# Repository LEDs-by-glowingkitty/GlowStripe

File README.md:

# GlowStripe PCB

## What is this project?

A stable LED stripe PCB with a separate trace for a button.

## Links

- [Schematic](https://github.com/glowingkitty/GlowStripe/blob/main/GlowLEDsPCB.pdf)
- [Interactive BOM](https://htmlpreview.github.io/?https://github.com/glowingkitty/GlowStripe/blob/main/bom/ibom.html)
- [PCB stencils](https://github.com/glowingkitty/GlowStripe/tree/main/PCB%20stencils)

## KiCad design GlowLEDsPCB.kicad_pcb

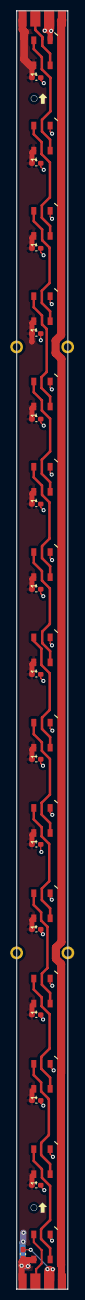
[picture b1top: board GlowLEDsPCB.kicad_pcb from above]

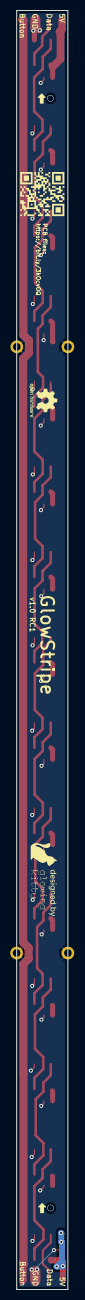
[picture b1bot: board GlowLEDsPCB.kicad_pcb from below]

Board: 2 copper layers, 10.0 x 250.0 mm, 43 parts (5 on the bottom side), 19 nets.

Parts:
C1, C2, C3, C4, C5, C6, C7, C8, C9, C10, C11, C12, C13, C14, C15: 0.1uf; C_0603_1608Metric_Pad1.08x0.95mm_HandSolder
D1, D2, D3, D4, D5, D6, D7, D8, D9, D10, D11, D12, D13, D14, D15: WS2812B; LED_WS2812B_PLCC4_5.0x5.0mm_P3.2mm
H1, H2, H3, H4: Castellated_hole; Castellated hole
OSHW logo: OSHW-Logo2_7.3x6mm_SilkScreen
U1, U2: Contact pads; LED strip connector 4pad small
designedby: LOGO
leddirectionarrow4, leddirectionarrow4#2, leddirectionarrow4#3, leddirectionarrow4#4: LOGO
qrcode: LOGO

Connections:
+5V: C1.1, C2.1, C3.1, C4.1, C5.1, C6.1, C7.1, C8.1, C9.1, C10.1, C11.1, C12.1, C13.1, C14.1, C15.1, D1.1 (VDD), D2.1 (VDD), D3.1 (VDD), D4.1 (VDD), D5.1 (VDD), D6.1 (VDD), D7.1 (VDD), D8.1 (VDD), D9.1 (VDD), D10.1 (VDD), D11.1 (VDD), D12.1 (VDD), D13.1 (VDD), D14.1 (VDD), D15.1 (VDD), U1.1 (5V), U2.1 (5V)
BUTTON: U1.4 (BUTTON), U2.4 (BUTTON)
GND: C1.2, C2.2, C3.2, C4.2, C5.2, C6.2, C7.2, C8.2, C9.2, C10.2, C11.2, C12.2, C13.2, C14.2, C15.2, D1.3 (VSS), D2.3 (VSS), D3.3 (VSS), D4.3 (VSS), D5.3 (VSS), D6.3 (VSS), D7.3 (VSS), D8.3 (VSS), D9.3 (VSS), D10.3 (VSS), D11.3 (VSS), D12.3 (VSS), D13.3 (VSS), D14.3 (VSS), D15.3 (VSS), H1.1, H2.1, H3.1, H4.1, U1.3 (GND), U2.3 (GND)
unnamed: D1.2 (DOUT), D2.4 (DIN)
unnamed: D1.4 (DIN), U1.2 (Data)
unnamed: D2.2 (DOUT), D3.4 (DIN)
unnamed: D3.2 (DOUT), D4.4 (DIN)
unnamed: D4.2 (DOUT), D5.4 (DIN)
unnamed: D5.2 (DOUT), D6.4 (DIN)
unnamed: D6.2 (DOUT), D7.4 (DIN)
unnamed: D7.2 (DOUT), D8.4 (DIN)
unnamed: D8.2 (DOUT), D9.4 (DIN)
unnamed: D10.2 (DOUT), D11.4 (DIN)
unnamed: D9.2 (DOUT), D10.4 (DIN)
unnamed: D11.2 (DOUT), D12.4 (DIN)
unnamed: D12.2 (DOUT), D13.4 (DIN)
unnamed: D13.2 (DOUT), D14.4 (DIN)
unnamed: D14.2 (DOUT), D15.4 (DIN)
unnamed: D15.2 (DOUT), U2.2 (Data)

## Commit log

2022-05-05 added first version of pcb
2022-05-05 fixed links
2022-05-05 fixed link
2022-05-06 added warning info
2022-06-05 increased pcb thickness and extended pads to edges
2022-06-14 fixed link and make pcb thicker and white
2022-06-21 updated to release candidate 1
2022-07-10 added tooling holes
2022-08-24 updated pcb
